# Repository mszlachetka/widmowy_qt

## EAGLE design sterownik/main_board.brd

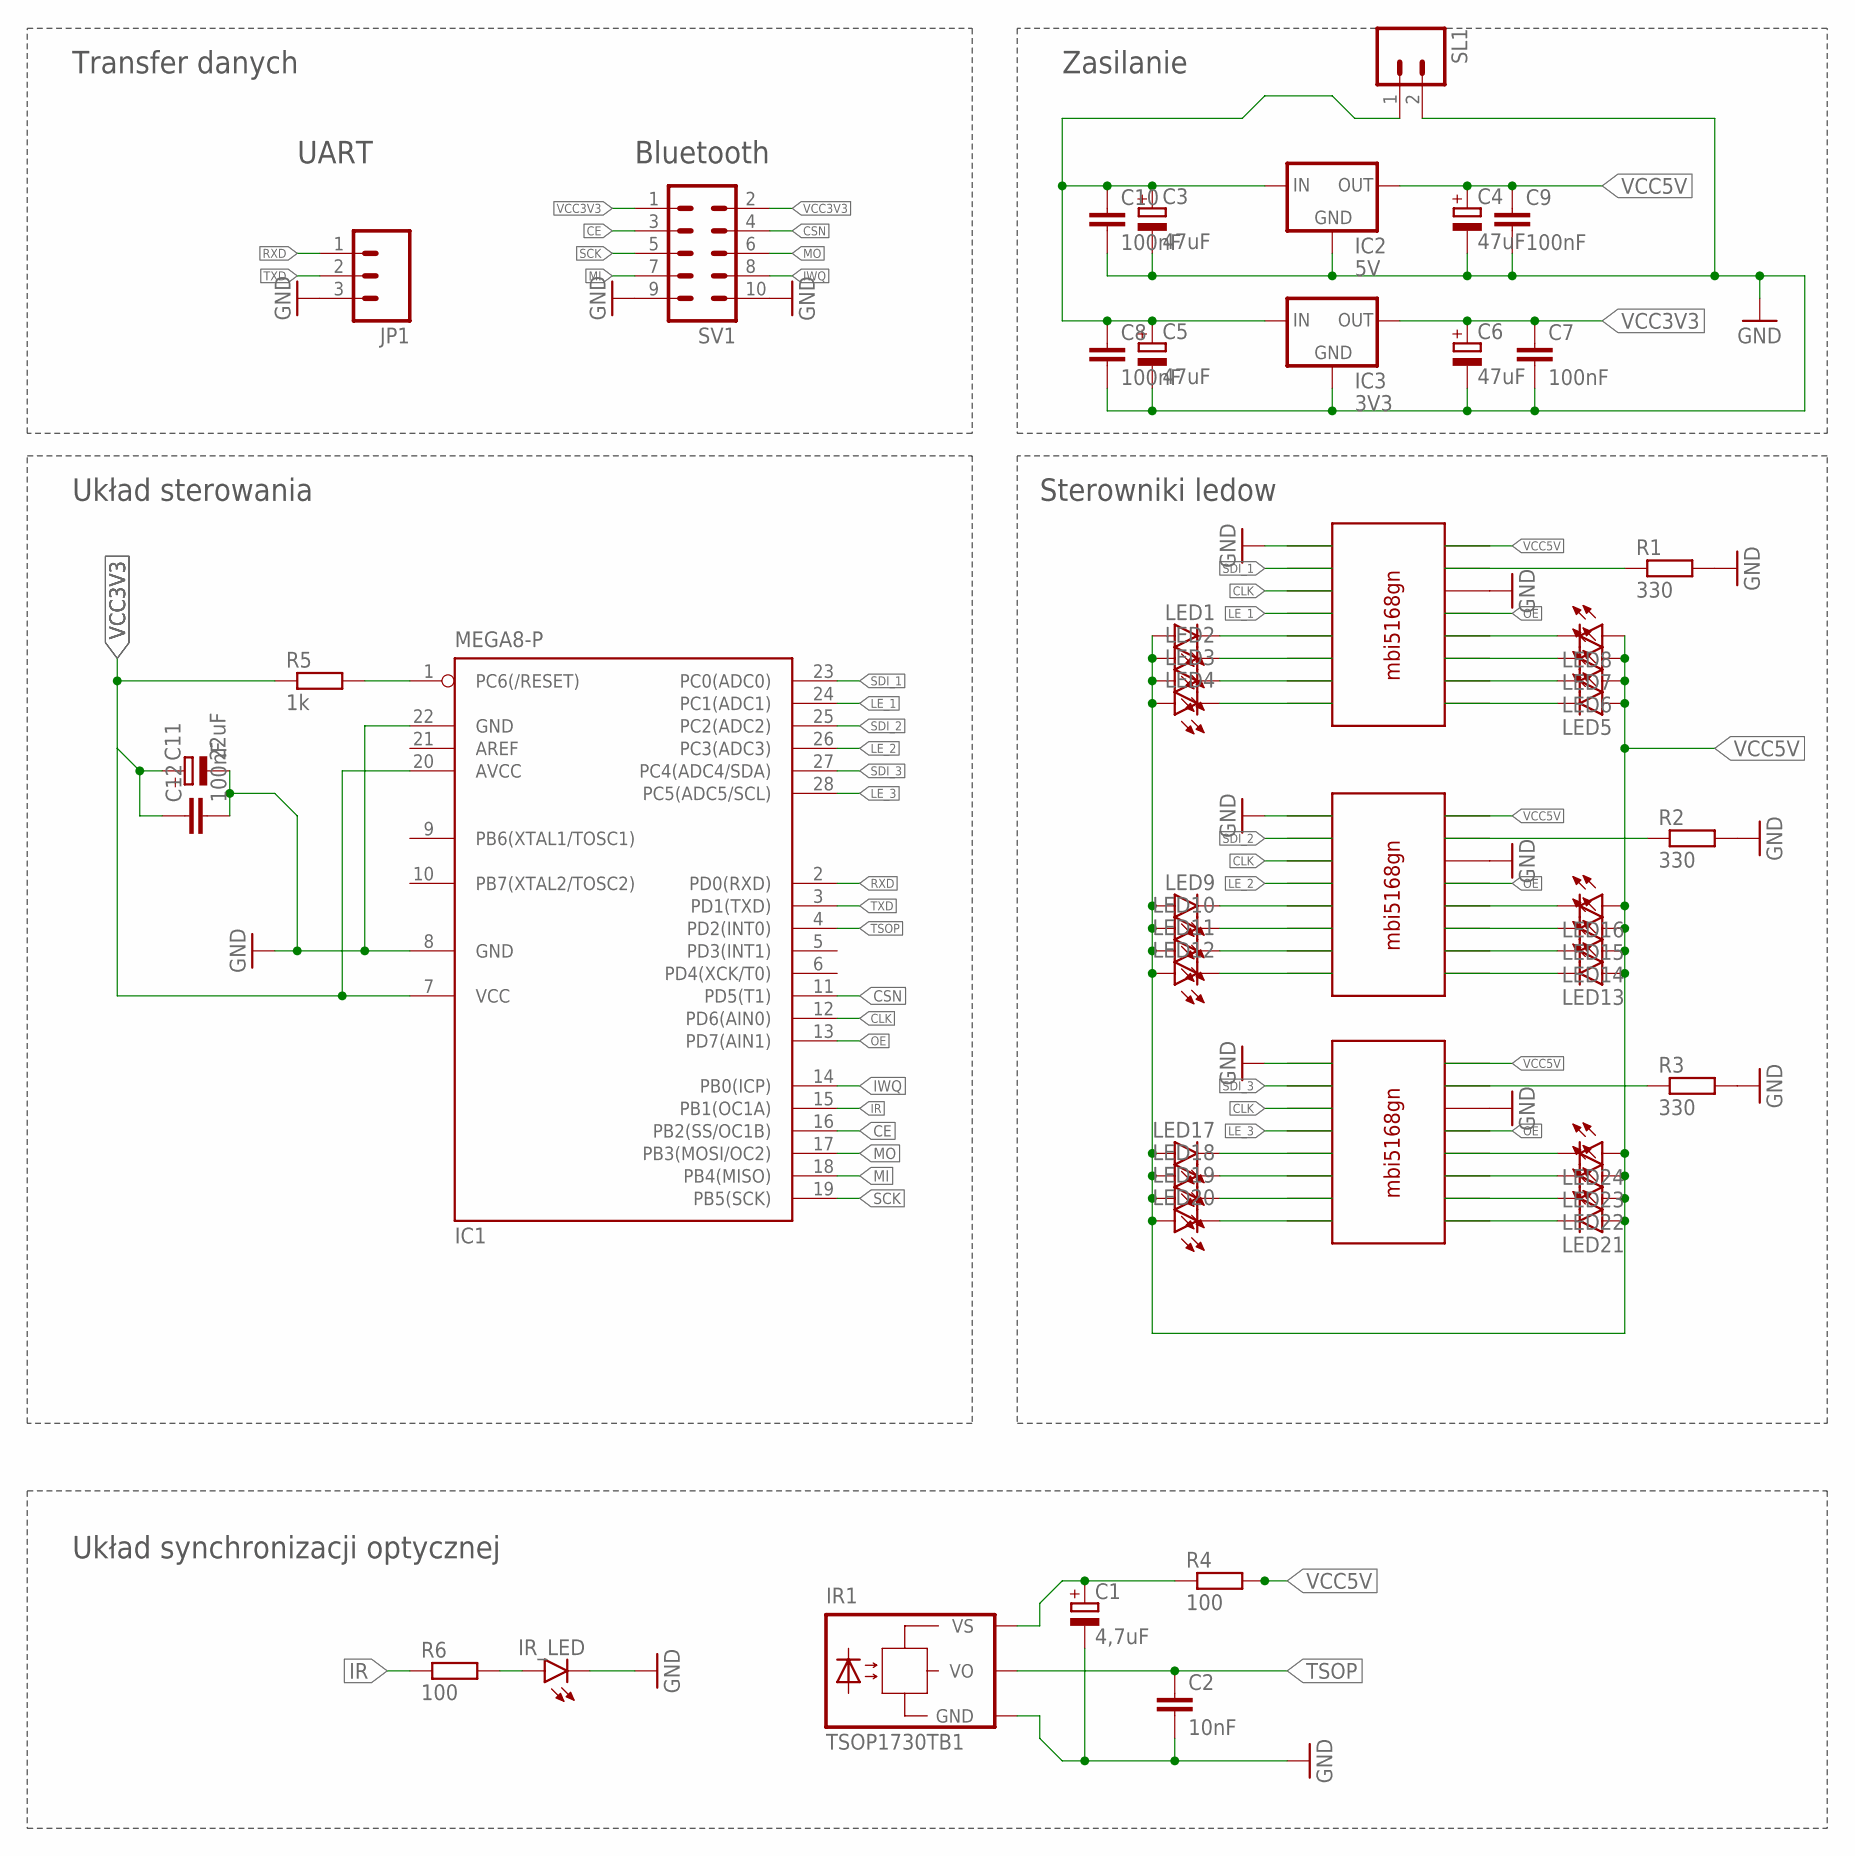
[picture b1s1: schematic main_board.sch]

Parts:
C1: 4,7uF; B45181A
C2: 10nF; C025-040X050
C3, C4, C5, C6: 47uF; B45181A
C7, C8, C9, C10: 100nF; C0805
C11: 22uF; B45181A
C12: 100nF; C025-040X050
IC1: MEGA8-P; DIL28-3
IC2: 5V; TO-220-ALT
IC3: 3V3; TO-220-ALT
IR1: TSOP1730TB1; TSOP17_TB1
IR_LED: LED5MM
JP1: M03PTH; 1X03
LED1, LED2, LED3, LED4, LED5, LED6, LED7, LED8, LED9, LED10, LED11, LED12, LED13, LED14, LED15, LED16, LED17, LED18, LED19, LED20, LED21, LED22, LED23, LED24: LED3MM
R1, R2, R3: 330; M0805
R4, R6: 100; M0805
R5: 1k; M0805
SL1: M02; 02P
SV1: MA05-2
U$1, U$2, U$3: MBI5168GN; DIL16

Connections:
CE: IC1.16 (PB2(SS/OC1B)), SV1.3
CLK: IC1.12 (PD6(AIN0)), U$1.CLK, U$2.CLK, U$3.CLK
CSN: IC1.11 (PD5(T1)), SV1.4
GND: C1.-, C2.2, C3.-, C4.-, C5.-, C6.-, C7.2, C8.2, C9.2, C10.2, C11.-, C12.2, IC1.8 (GND), IC1.22 (GND), IC2.GND, IC3.GND, IR1.GND, IR_LED.K (C), JP1.3, R1.2, R2.2, R3.2, SL1.2, SV1.9, SV1.10, U$1.GND, U$2.GND, U$3.GND
IR: IC1.15 (PB1(OC1A)), R6.1
IWQ: IC1.14 (PB0(ICP)), SV1.8
LE_1: IC1.24 (PC1(ADC1)), U$1.LE
LE_2: IC1.26 (PC3(ADC3)), U$2.LE
LE_3: IC1.28 (PC5(ADC5/SCL)), U$3.LE
MI: IC1.18 (PB4(MISO)), SV1.7
MO: IC1.17 (PB3(MOSI/OC2)), SV1.6
unnamed: LED8.K (C), U$1.OUT7
unnamed: LED7.K (C), U$1.OUT6
unnamed: LED6.K (C), U$1.OUT5
unnamed: LED5.K (C), U$1.OUT4
unnamed: LED4.K (C), U$1.OUT3
unnamed: LED3.K (C), U$1.OUT2
unnamed: LED2.K (C), U$1.OUT1
unnamed: LED1.K (C), U$1.OUT0
unnamed: LED17.K (C), U$3.OUT0
unnamed: LED18.K (C), U$3.OUT1
unnamed: LED19.K (C), U$3.OUT2
unnamed: LED20.K (C), U$3.OUT3
unnamed: LED21.K (C), U$3.OUT4
unnamed: LED22.K (C), U$3.OUT5
unnamed: LED23.K (C), U$3.OUT6
unnamed: LED24.K (C), U$3.OUT7
unnamed: LED13.K (C), U$2.OUT4
unnamed: LED14.K (C), U$2.OUT5
unnamed: LED15.K (C), U$2.OUT6
unnamed: LED16.K (C), U$2.OUT7
unnamed: LED12.K (C), U$2.OUT3
unnamed: LED11.K (C), U$2.OUT2
unnamed: LED10.K (C), U$2.OUT1
unnamed: LED9.K (C), U$2.OUT0
unnamed: C3.+, C5.+, C8.1, C10.1, IC2.IN, IC3.IN, SL1.1
unnamed: R1.1, U$1.R-EXT
unnamed: C1.+, IR1.VS, R4.1
unnamed: R3.1, U$3.R-EXT
unnamed: R2.1, U$2.R-EXT
unnamed: IR_LED.A, R6.2
unnamed: IC1.1 (PC6(/RESET)), R5.2
OE: IC1.13 (PD7(AIN1)), U$1.OE, U$2.OE, U$3.OE
RXD: IC1.2 (PD0(RXD)), JP1.1
SCK: IC1.19 (PB5(SCK)), SV1.5
SDI_1: IC1.23 (PC0(ADC0)), U$1.SDI
SDI_2: IC1.25 (PC2(ADC2)), U$2.SDI
SDI_3: IC1.27 (PC4(ADC4/SDA)), U$3.SDI
TSOP: C2.1, IC1.4 (PD2(INT0)), IR1.VO
TXD: IC1.3 (PD1(TXD)), JP1.2
VCC3V3: C6.+, C7.1, C11.+, C12.1, IC1.7 (VCC), IC1.20 (AVCC), IC3.OUT, R5.1, SV1.1, SV1.2
VCC5V: C4.+, C9.1, IC2.OUT, LED1.A, LED2.A, LED3.A, LED4.A, LED5.A, LED6.A, LED7.A, LED8.A, LED9.A, LED10.A, LED11.A, LED12.A, LED13.A, LED14.A, LED15.A, LED16.A, LED17.A, LED18.A, LED19.A, LED20.A, LED21.A, LED22.A, LED23.A, LED24.A, R4.2, U$1.VCC, U$2.VCC, U$3.VCC

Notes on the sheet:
Sterowniki ledow
Układ sterowania
Zasilanie
Transfer danych
UART
Bluetooth
Układ synchronizacji optycznej

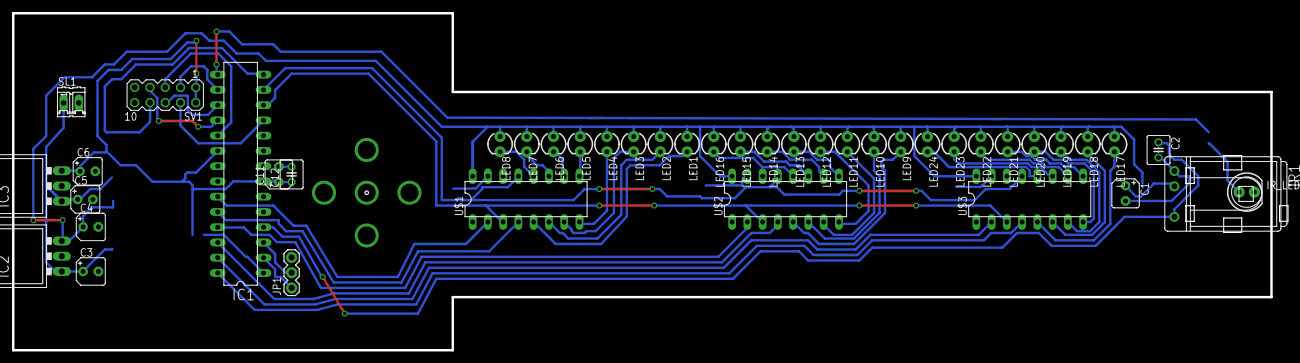
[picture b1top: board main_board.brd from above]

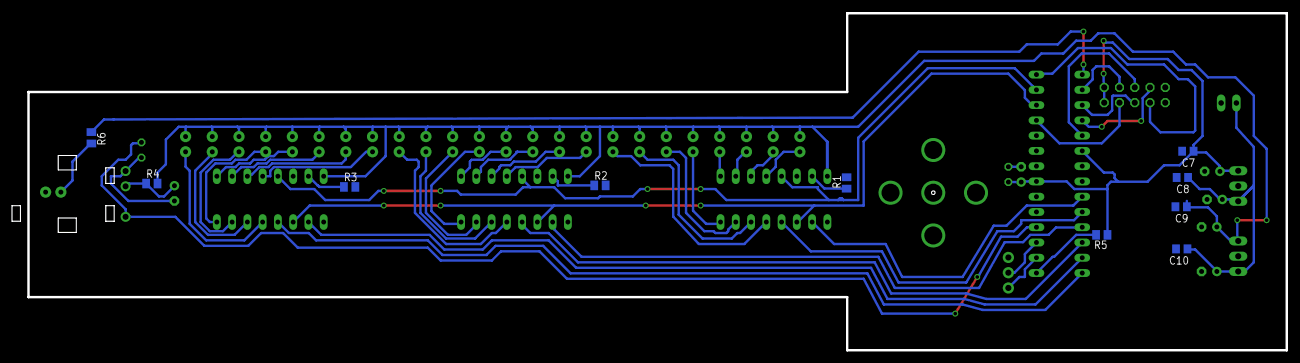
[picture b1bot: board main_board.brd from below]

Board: 2 copper layers, 211.9 x 56.1 mm, 53 parts (10 on the bottom side), 52 nets.

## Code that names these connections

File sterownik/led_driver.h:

/*
 * led_driver.h
 *
 *  Created on: Nov 25, 2014
 *      Author: Michal
 */

#ifndef LED_DRIVER_H_
#define LED_DRIVER_H_

#include "own_timer.h"

#define CLK 2
#define OE 5


#define SDI_2 0
#define LE_2 1

#define LE_1 4
#define SDI_1 3

void send_LED_char(char data , int sdi, int le)
{
	int i=0;

	PORTB|=(1<<le);
	for(i=0;i<8;i++)
	{
		if(data&(1<<i))
		{
			PORTB|=(1<<sdi);
			czas_us(1);
			PORTB|=(1<<CLK);
			czas_us(1);
			PORTB&=~(1<<sdi);
			czas_us(1);
			PORTB&=~(1<<CLK);
			czas_us(1);
		}
		else
			{
			PORTB|=(1<<CLK);
			czas_us(2);
			PORTB&=~(1<<CLK);
			czas_us(2);
			}
	}

czas_us(200);
	PORTB&=~(1<<le);


}



#endif /* LED_DRIVER_H_ */

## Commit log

2014-11-05 :confetti_ball: Added .gitattributes & .gitignore files
2014-11-05 symulator wyswietlacza widmowego
    +do testów
    -bez przesyłu danych
2014-11-28 Można przesłac obraz , wybrać ilosc ledow
2014-11-30 dodane save/load
2015-02-11 maly update
2015-02-11 porzadki
2015-09-27 entire core
2015-10-23 2 strips , good work for 15km/h - 25km/h
2015-11-13 version 1.0

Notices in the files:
parts and their libraries:
SparkFun-LED: Licensing: Creative Commons ShareAlike 4.0 International - https://creativecommons.org/licenses/by-sa/4.0
